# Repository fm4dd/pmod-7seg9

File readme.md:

## 7SEG9 PMOD

### Description

This PMOD provides a 9-digit (3x3) 7-segment LED display output to FPGA designs via a single row PMOD connector. The LED segments are driven by the TM1640 LED driver IC from Titan Microelectronics. The TM1640 can only handle "common cathode" display types. It implements the required multiplexing, LED resistance and 8-level output power control that greatly reduces the passive components needed to drive LED displays. The TM1640 driver IC interfaces with application logic through a simplified two-wire serial protocol that has similarities with I2C. A small DCDC boost converter SGM6603 raises the 3.3V PMOD voltage to the 5V operating voltage needed by the TM1640 driver IC.

http://fpga.fm4dd.com/

*Note:* The 7SEG9 PMOD draws 220-250mA current over 9 digits. During power on/off, the peak current can reach 500mA. This needs attention for boards with weak power supply.

### Schematic

### PCB Gerber

[7SEG4 PMOD Gerber V1.2](fabfiles/v12/20200520-7seg9-gerber-v12.zip)

### Pin Assignments

<table>
  <tr><th>PMOD Pinout</th><th>Pin</th><th>Label</th><th>Function</th></tr>
  <tr><td rowspan="6"></td>
    <td>1</td><td>n/c</td><td>(not connected)</td></tr>
    <tr><td>2</td><td>n/c</td><td>(not connected)</td></tr>
    <tr><td>3</td><td>tm_din</td><td>LED control data</td></tr>
    <tr><td>4</td><td>tm_clk</td><td>Bus Clock (<1MHz)</td></tr>
    <tr><td>5</td><td>GND</td><td>PMOD Power</td></tr>
    <tr><td>6</td><td>3V3</td><td>PMOD Power</td></tr>
</table>

### Example Code

The following platform code examples demonstrate the board function for quick verification.

| Platform | Test Program location                | Description                                                  |
|----------|-----------------------------------------|--------------------------------------------------------------|
| Arduino IDE |[examples/arduino](examples/arduino) | Arduino IDE code (tested on PMOD2RPI Seeedstudio XIAO) |
| Raspberry Pi|[examples/pi-tm1640](examples/pi-tm1640) | Linux control program in 'C', using the libgpiod interface |
|IceBreaker|[examples/icebreaker](examples/icebreaker)| Verilog project for the IceBreaker FPGA (Lattice iCE40 FPGA family) |
| ULX3S    |[examples/ulx3s](examples/ulx3s)          | Verilog project for Radiona ULX3S FPGA (Lattice ECP5 FPGA family) |
| GateMate |[examples/gatemate](examples/gatemate)    | Verilog project for the Cologne Chip Gatemate E1 FPGA board |

### PMOD-7Seg9 Function Tests

The oscilloscope visualizes the protocol data transmission. Blue = data signal, Orange = clock signal.

7SEG9 PMOD connected to a Icebreaker v1.0 board, during protocol analysis

7SEG9 PMOD, connected to the Icebreaker FPGA board

Two 7seg9 PMODs, connected to a ULX3S (Lattice ECP5 85K) board

Two 7seg9 PMODs, connected to a Raspberry Pi via the PMOD2RPI interface board

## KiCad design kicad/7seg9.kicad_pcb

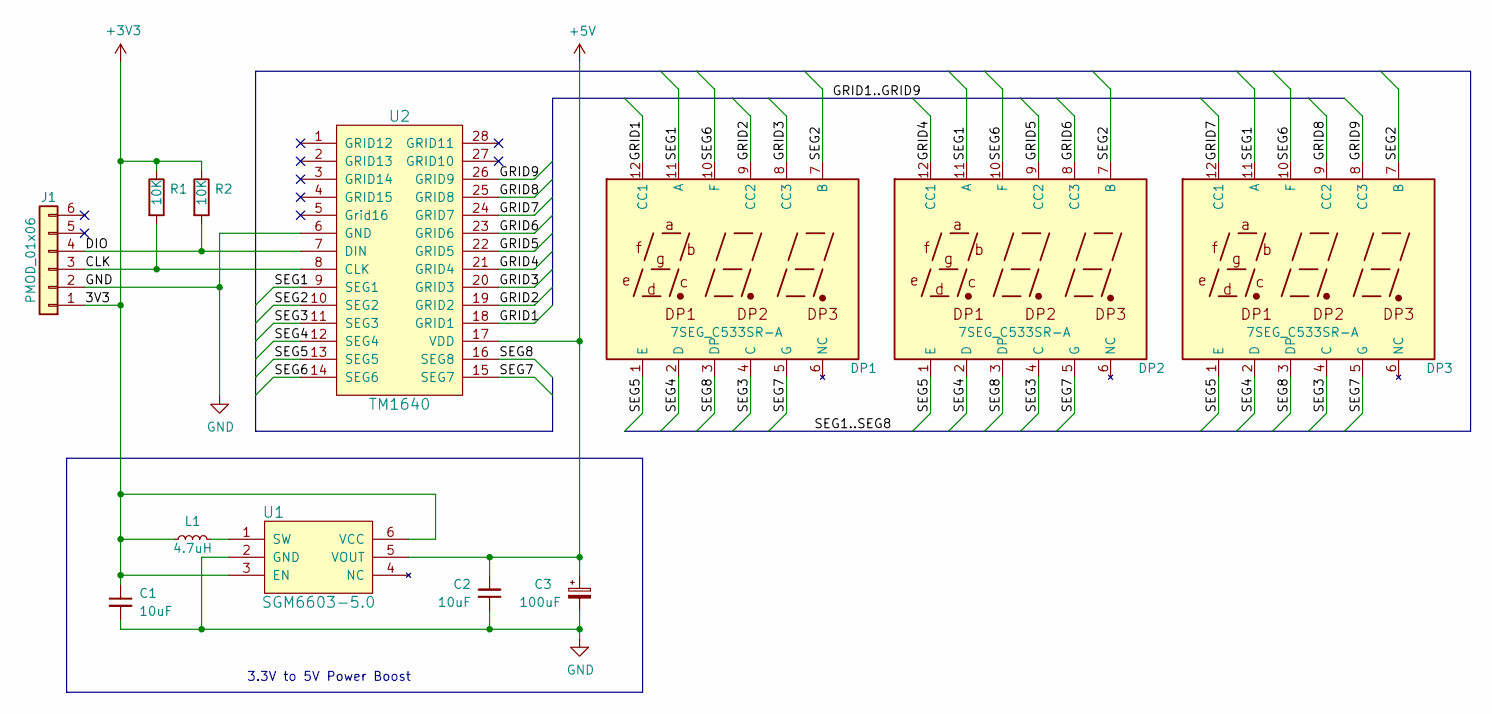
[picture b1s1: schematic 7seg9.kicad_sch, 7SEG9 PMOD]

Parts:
C1, C2: 10uF; C_0603_1608Metric
C3: 100uF; CP_Elec_6.3x5.4
DP1, DP2, DP3: 7SEG_C533SR-A; 7SEG_CS533SR-A
J1: PMOD_01x06; PinHeader_1x06_P2.54mm_Horizontal
L1: 4.7uH; L_0603_1608Metric
R1, R2: 10K; R_0603_1608Metric
U1: SGM6603-5.0; SOT-23-6
U2: TM1640; SOP-28_7.5x17.9mm_P1.27mm

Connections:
+3V3: C1.1, J1.1, L1.1, R1.1, R2.1, U1.3 (EN), U1.6 (VCC)
+5V: C2.2, C3.1, U1.5 (VOUT), U2.17 (VDD)
/CLK: J1.3, R1.2, U2.8 (CLK)
/DIO: J1.4, R2.2, U2.7 (DIN)
/GRID1: DP1.12 (CC1), U2.18 (GRID1)
/GRID2: DP1.9 (CC2), U2.19 (GRID2)
/GRID3: DP1.8 (CC3), U2.20 (GRID3)
/GRID4: DP2.12 (CC1), U2.21 (GRID4)
/GRID5: DP2.9 (CC2), U2.22 (GRID5)
/GRID6: DP2.8 (CC3), U2.23 (GRID6)
/GRID7: DP3.12 (CC1), U2.24 (GRID7)
/GRID8: DP3.9 (CC2), U2.25 (GRID8)
/GRID9: DP3.8 (CC3), U2.26 (GRID9)
/SEG1: DP1.11 (A), DP2.11 (A), DP3.11 (A), U2.9 (SEG1)
/SEG2: DP1.7 (B), DP2.7 (B), DP3.7 (B), U2.10 (SEG2)
/SEG3: DP1.4 (C), DP2.4 (C), DP3.4 (C), U2.11 (SEG3)
/SEG4: DP1.2 (D), DP2.2 (D), DP3.2 (D), U2.12 (SEG4)
/SEG5: DP1.1 (E), DP2.1 (E), DP3.1 (E), U2.13 (SEG5)
/SEG6: DP1.10 (F), DP2.10 (F), DP3.10 (F), U2.14 (SEG6)
/SEG7: DP1.5 (G), DP2.5 (G), DP3.5 (G), U2.15 (SEG7)
/SEG8: DP1.3 (DP), DP2.3 (DP), DP3.3 (DP), U2.16 (SEG8)
GND: C1.2, C2.1, C3.2, J1.2, U1.2 (GND), U2.6 (GND)
unnamed: L1.2, U1.1 (SW)

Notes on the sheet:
3.3V to 5V Power Boost

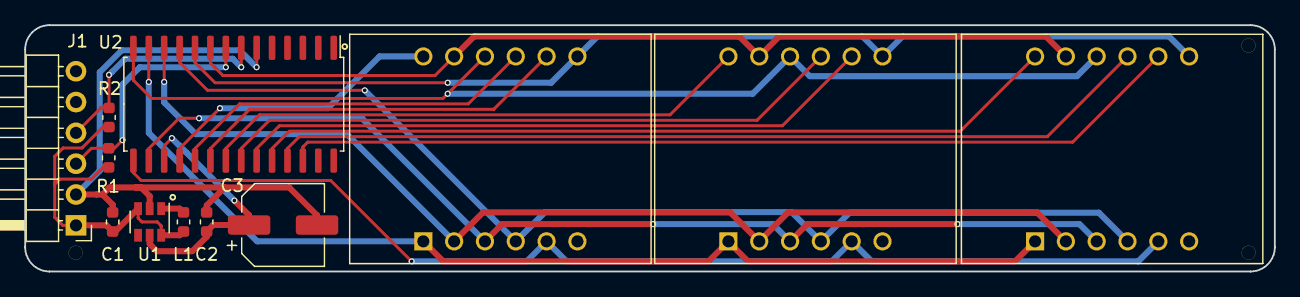
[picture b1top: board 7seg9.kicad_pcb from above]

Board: 2 copper layers, 103.0 x 20.3 mm, 15 parts (0 on the bottom side), 23 nets.

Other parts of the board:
TOOLING_HOLE_1.152: TOOL2; SMD_TOOLING_HOLE_1.152mm
TOOLING_HOLE_1.152#2: TOOL3; SMD_TOOLING_HOLE_1.152mm
TOOLING_HOLE_1.152#3: TOOL1; SMD_TOOLING_HOLE_1.152mm

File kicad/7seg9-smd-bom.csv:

"Comment","Designator","Footprint","LCSC"
"10uF","C1, C2","Capacitor_SMD:C_0603_1608Metric",""
"100uF","C3","Capacitor_SMD:CP_Elec_6.3x5.4",""
"7SEG_C533SR-A","DP1, DP2, DP3","01_FM4DD:7SEG_CS533SR-A",""
"PMOD_01x06","J1","Connector_PinHeader_2.54mm:PinHeader_1x06_P2.54mm_Horizontal",""
"4.7uH","L1","Inductor_SMD:L_0603_1608Metric",""
"10K","R1, R2","Resistor_SMD:R_0603_1608Metric",""
"SGM6603-5.0","U1","Package_TO_SOT_SMD:SOT-23-6",""
"TM1640","U2","01_FM4DD:SOP-28_7.5x17.9mm_P1.27mm",""

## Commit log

2020-08-06 initial upload
2020-08-06 add lang ident
2020-11-30 Add ULX3S example
2021-10-10 add Linux driver example
2021-10-24 add RPi workflow
2023-11-03 Kicad and OSS toolchain version upgrades
2023-11-03 add Gatemate FPGA example
2023-11-04 documentation update
2023-11-04 Arduino example
2023-11-05 Update rpi.yml
    to manually trigger the workflow
2023-11-12 update FPGA examples
2026-02-14 convert to Gatemate OSS toolchain, update verilog examples

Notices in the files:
kicad/7seg9.kicad_pcb:
License: CC-BY-SA 4.0
(c) 2020 FM4DD
